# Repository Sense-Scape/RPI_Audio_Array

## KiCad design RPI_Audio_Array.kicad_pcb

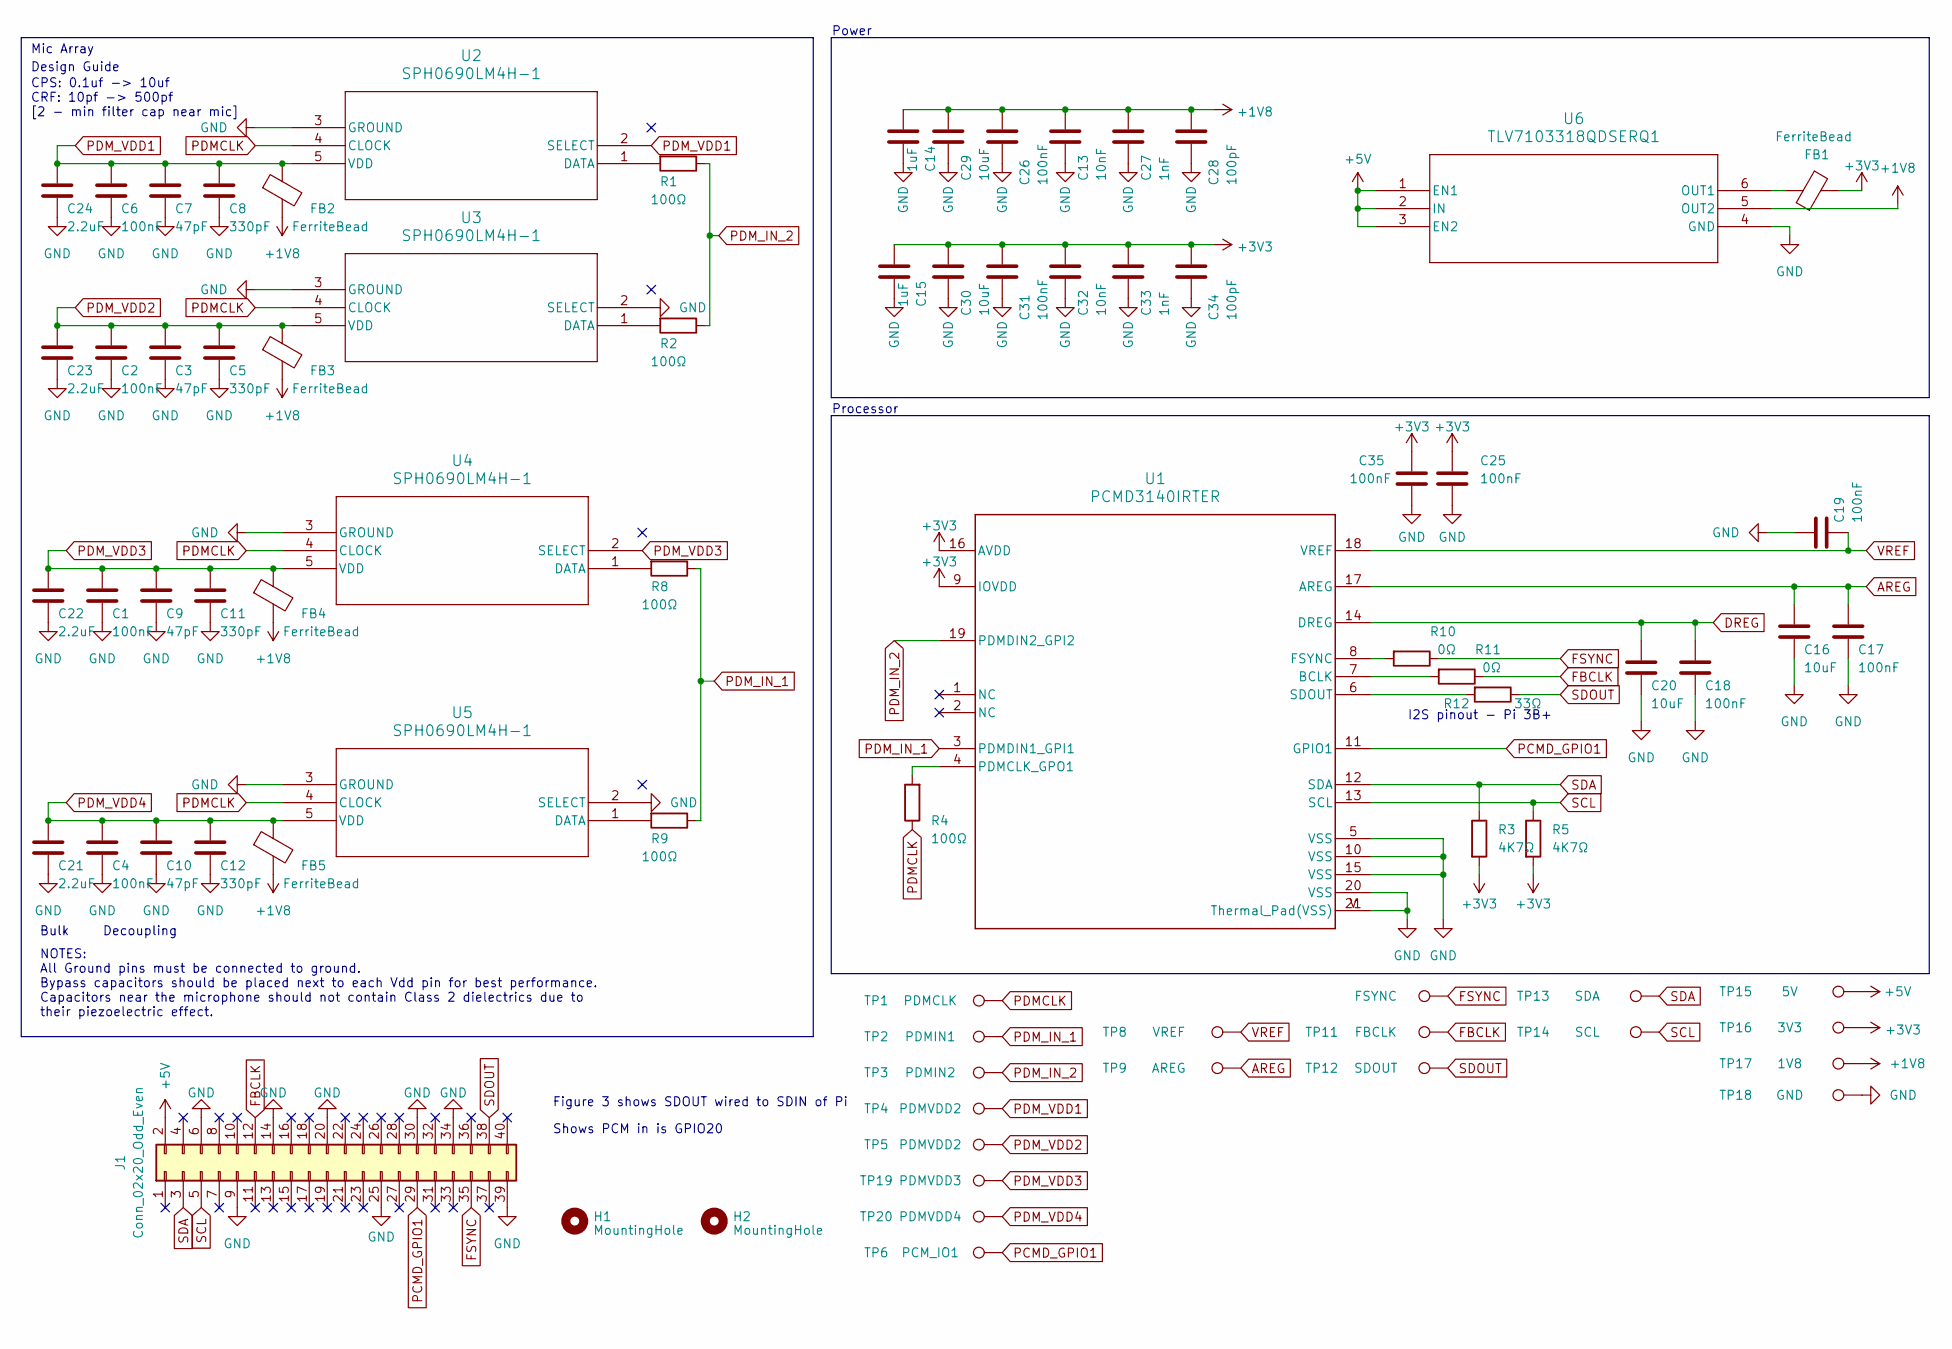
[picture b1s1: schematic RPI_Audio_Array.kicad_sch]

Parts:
C1, C2, C4, C6, C17, C18, C19, C25, C26, C31, C35: 100nF; C_0603_1608Metric; lcsc C14663
C3, C7, C9, C10: 47pF; C_0603_1608Metric; lcsc C1671
C5, C8, C11, C12: 330pF; C_0603_1608Metric; lcsc C1664
C13, C32: 10nF; C_0603_1608Metric; lcsc C57112
C14, C15: 1uF; C_0603_1608Metric; lcsc C15849
C16, C20: 10uF; C_0805_2012Metric; lcsc C440198
C21, C22, C23, C24: 2.2uF; C_0805_2012Metric; lcsc C377773
C27, C33: 1nF; C_0603_1608Metric; lcsc C1588
C28, C34: 100pF; C_0603_1608Metric; lcsc C14858
C29, C30: 10uF; C_1206_3216Metric; lcsc C13585
FB1, FB2, FB3, FB4, FB5: FerriteBead; L_0805_2012Metric; lcsc C1017
H1, H2: MountingHole; MountingHole_2.7mm_M2.5; lcsc DNP
J1: Conn_02x20_Odd_Even; PinSocket_2x20_P2.54mm_Vertical; lcsc DNP
R1, R2, R4, R8, R9: 100Ω; R_0603_1608Metric; lcsc C22775
R3, R5: 4K7Ω; R_0603_1608Metric; lcsc C23162
R10, R11: 0Ω; R_0603_1608Metric; lcsc C21189
R12: 33Ω; R_0603_1608Metric; lcsc C23140
TP1: PDMCLK; TestPoint_Plated_Hole_D2.0mm; lcsc DNP
TP2: PDMIN1; TestPoint_Plated_Hole_D2.0mm; lcsc DNP
TP3: PDMIN2; TestPoint_Plated_Hole_D2.0mm; lcsc DNP
TP4, TP5: PDMVDD2; TestPoint_Plated_Hole_D2.0mm; lcsc DNP
TP6: PCM_IO1; TestPoint_Plated_Hole_D2.0mm; lcsc DNP
TP8: VREF; TestPoint_Plated_Hole_D2.0mm; lcsc DNP
TP9: AREG; TestPoint_Plated_Hole_D2.0mm; lcsc DNP
TP10: FSYNC; TestPoint_Plated_Hole_D2.0mm; lcsc DNP
TP11: FBCLK; TestPoint_Plated_Hole_D2.0mm; lcsc DNP
TP12: SDOUT; TestPoint_Plated_Hole_D2.0mm; lcsc DNP
TP13: SDA; TestPoint_Plated_Hole_D2.0mm; lcsc DNP
TP14: SCL; TestPoint_Plated_Hole_D2.0mm; lcsc DNP
TP15: 5V; TestPoint_Plated_Hole_D2.0mm; lcsc DNP
TP16: 3V3; TestPoint_Plated_Hole_D2.0mm; lcsc DNP
TP17: 1V8; TestPoint_Plated_Hole_D2.0mm; lcsc DNP
TP18: GND; TestPoint_Plated_Hole_D2.0mm; lcsc DNP
TP19: PDMVDD3; TestPoint_Plated_Hole_D2.0mm; lcsc DNP
TP20: PDMVDD4; TestPoint_Plated_Hole_D2.0mm; lcsc DNP
U1: PCMD3140IRTER; RTE0020A-MFG; lcsc DNP (Not Available)
U2, U3, U4, U5: SPH0690LM4H-1; SPH0690LM4H-1_KNO; lcsc DNP (Not Available)
U6: TLV7103318QDSERQ1; DSE6_TEX; lcsc DNP (Not Available)

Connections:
+1V8: C13.1, C14.1, C26.1, C27.1, C28.1, C29.1, FB2.2, FB3.2, FB4.2, FB5.2, TP17.1, U6.5 (OUT2)
+3V3: C15.1, C25.1, C30.1, C31.1, C32.1, C33.1, C34.1, C35.1, FB1.2, R3.2, R5.2, TP16.1, U1.9 (IOVDD), U1.16 (AVDD)
+5V: J1.2, TP15.1, U6.1 (EN1), U6.2 (IN), U6.3 (EN2)
AREG: C16.1, C17.1, TP9.1, U1.17 (AREG)
DREG: C18.1, C20.1, U1.14 (DREG)
FBCLK: J1.12, R11.1, TP11.1
FSYNC: J1.35, R10.1, TP10.1
GND: C1.2, C2.2, C3.2, C4.2, C5.2, C6.2, C7.2, C8.2, C9.2, C10.2, C11.2, C12.2, C13.2, C14.2, C15.2, C16.2, C17.2, C18.2, C19.1, C20.2, C21.2, C22.2, C23.2, C24.2, C25.2, C26.2, C27.2, C28.2, C29.2, C30.2, C31.2, C32.2, C33.2, C34.2, C35.2, J1.6, J1.9, J1.14, J1.20, J1.25, J1.30, J1.34, J1.39, TP18.1, U1.5 (VSS), U1.10 (VSS), U1.15 (VSS), U1.20 (VSS), U1.21 (Thermal_Pad(VSS)), U1.V (Thermal_Pad(VSS)), U2.3 (GROUND), U3.2 (SELECT), U3.3 (GROUND), U4.3 (GROUND), U5.2 (SELECT), U5.3 (GROUND), U6.4 (GND)
unnamed: R11.2, U1.7 (BCLK)
unnamed: R10.2, U1.8 (FSYNC)
unnamed: R4.2, U1.4 (PDMCLK_GPO1)
unnamed: R12.2, U1.6 (SDOUT)
unnamed: R1.2, U2.1 (DATA)
unnamed: R2.2, U3.1 (DATA)
unnamed: R8.2, U4.1 (DATA)
unnamed: R9.2, U5.1 (DATA)
unnamed: FB1.1, U6.6 (OUT1)
PCMD_GPIO1: J1.29, TP6.1, U1.11 (GPIO1)
PDMCLK: R4.1, TP1.1, U2.4 (CLOCK), U3.4 (CLOCK), U4.4 (CLOCK), U5.4 (CLOCK)
PDM_IN_1: R8.1, R9.1, TP2.1, U1.3 (PDMDIN1_GPI1)
PDM_IN_2: R1.1, R2.1, TP3.1, U1.19 (PDMDIN2_GPI2)
PDM_VDD1: C6.1, C7.1, C8.1, C24.1, FB2.1, TP4.1, U2.2 (SELECT), U2.5 (VDD)
PDM_VDD2: C2.1, C3.1, C5.1, C23.1, FB3.1, TP5.1, U3.5 (VDD)
PDM_VDD3: C1.1, C9.1, C11.1, C22.1, FB4.1, TP19.1, U4.2 (SELECT), U4.5 (VDD)
PDM_VDD4: C4.1, C10.1, C12.1, C21.1, FB5.1, TP20.1, U5.5 (VDD)
SCL: J1.5, R5.1, TP14.1, U1.13 (SCL)
SDA: J1.3, R3.1, TP13.1, U1.12 (SDA)
SDOUT: J1.38, R12.1, TP12.1
VREF: C19.2, TP8.1, U1.18 (VREF)

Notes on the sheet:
Bulk
I2S pinout - Pi 3B+
CPS: 0.1uf -> 10uf CRF: 10pf -> 500pf [2 - min filter cap near mic]
Mic Array
Power
Figure 3 shows SDOUT wired to SDIN of Pi
Shows PCM in is GPIO20
Decoupling
NOTES: All Ground pins must be connected to ground. Bypass capacitors should be placed next to each Vdd pin for best performance. Capacitors near the microphone should not contain Class 2 dielectrics due to their piezoelectric effect.
Design Guide
Processor

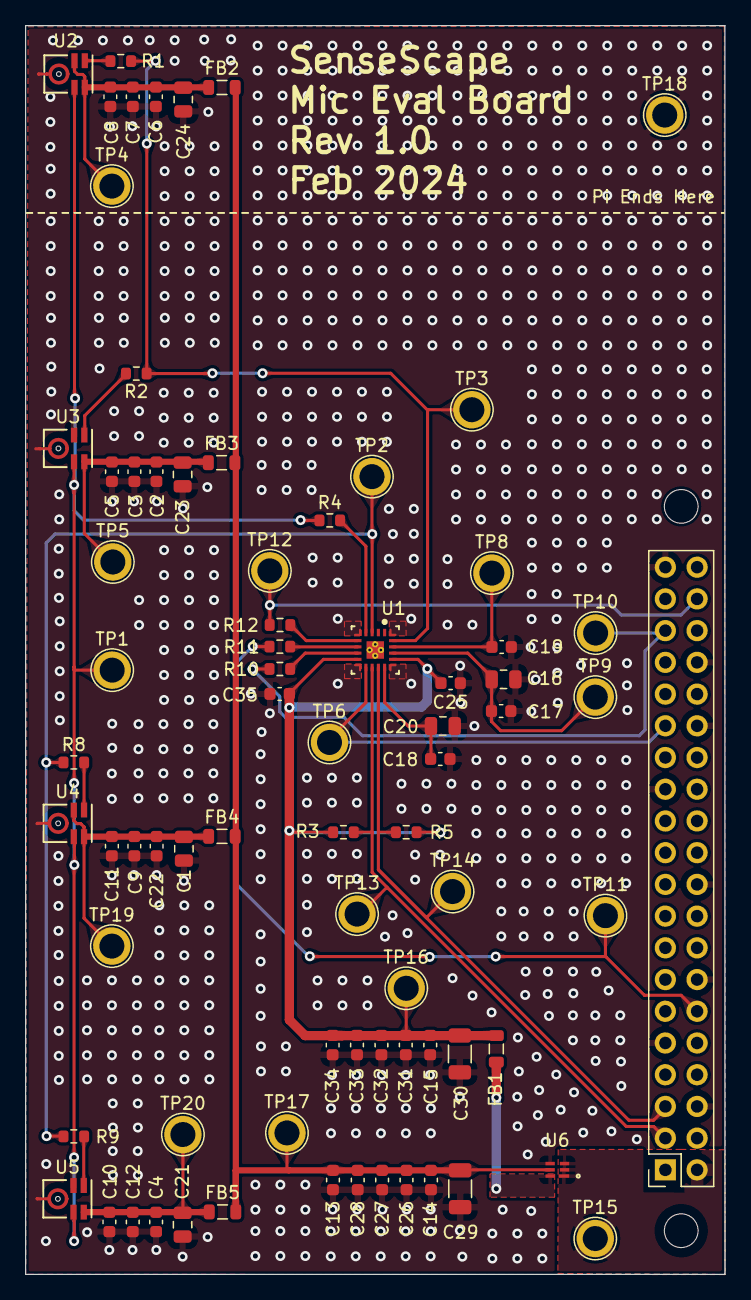
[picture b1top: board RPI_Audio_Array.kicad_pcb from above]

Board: 2 copper layers, 56.0 x 100.0 mm, 78 parts (0 on the bottom side), 29 nets.

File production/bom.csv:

Designator,Footprint,Quantity,Value,LCSC Part #
"C1, C17, C18, C19, C2, C25, C26, C31, C35, C4, C6",0603,11,100nF,
"C10, C3, C7, C9",0603,4,47pF,
"C11, C12, C5, C8",0603,4,330pF,
"C13, C32",0603,2,10nF,
"C14, C15",0603,2,1uF,
"C16, C20",0805,2,10uF,
"C21, C22, C23, C24",0805,4,2.2uF,
"C27, C33",0603,2,1nF,
"C28, C34",0603,2,100pF,
"C29, C30",1206,2,10uF,
"FB1, FB2, FB3, FB4, FB5",0805,5,FerriteBead,
"H1, H2",MountingHole_2.7mm_M2.5,2,MountingHole,
J1,PinSocket_2x20_P2.54mm_Vertical,1,Conn_02x20_Odd_Even,
"R1, R2, R4, R8, R9",0603,5,100Ω,
"R10, R11",0603,2,0Ω,
R12,0603,1,33Ω,
"R3, R5",0603,2,4K7Ω,
TP1,TestPoint_Plated_Hole_D2.0mm,1,PDMCLK,
TP10,TestPoint_Plated_Hole_D2.0mm,1,FSYNC,
TP11,TestPoint_Plated_Hole_D2.0mm,1,FBCLK,
TP12,TestPoint_Plated_Hole_D2.0mm,1,SDOUT,
TP13,TestPoint_Plated_Hole_D2.0mm,1,SDA,
TP14,TestPoint_Plated_Hole_D2.0mm,1,SCL,
TP15,TestPoint_Plated_Hole_D2.0mm,1,5V,
TP16,TestPoint_Plated_Hole_D2.0mm,1,3V3,
TP17,TestPoint_Plated_Hole_D2.0mm,1,1V8,
TP18,TestPoint_Plated_Hole_D2.0mm,1,GND,
TP19,TestPoint_Plated_Hole_D2.0mm,1,PDMVDD3,
TP2,TestPoint_Plated_Hole_D2.0mm,1,PDMIN1,
TP20,TestPoint_Plated_Hole_D2.0mm,1,PDMVDD4,
TP3,TestPoint_Plated_Hole_D2.0mm,1,PDMIN2,
"TP4, TP5",TestPoint_Plated_Hole_D2.0mm,2,PDMVDD2,
TP6,TestPoint_Plated_Hole_D2.0mm,1,PCM_IO1,
TP8,TestPoint_Plated_Hole_D2.0mm,1,VREF,
TP9,TestPoint_Plated_Hole_D2.0mm,1,AREG,
U1,RTE0020A-MFG,1,PCMD3140IRTER,
"U2, U3, U4, U5",SPH0690LM4H-1_KNO,4,SPH0690LM4H-1,
U6,DSE6_TEX,1,TLV7103318QDSERQ1,

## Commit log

2024-02-07 Feat: Fist commit
2024-02-11 Fix: Schemtatic fixes
2024-02-11 Chore: Updating PCB
2024-02-14 Fix: making further changes to bugs in schematic
2024-02-15 Fix: Removing extra cap
2024-02-17 Feat: Rerouting PCB
2024-02-17 Feat: adding more routing
2024-02-18 Chore: To fix drc issues
2024-02-19 Feat: Resolving all DRC warnings
2024-02-19 updated PCB and schematic for review
